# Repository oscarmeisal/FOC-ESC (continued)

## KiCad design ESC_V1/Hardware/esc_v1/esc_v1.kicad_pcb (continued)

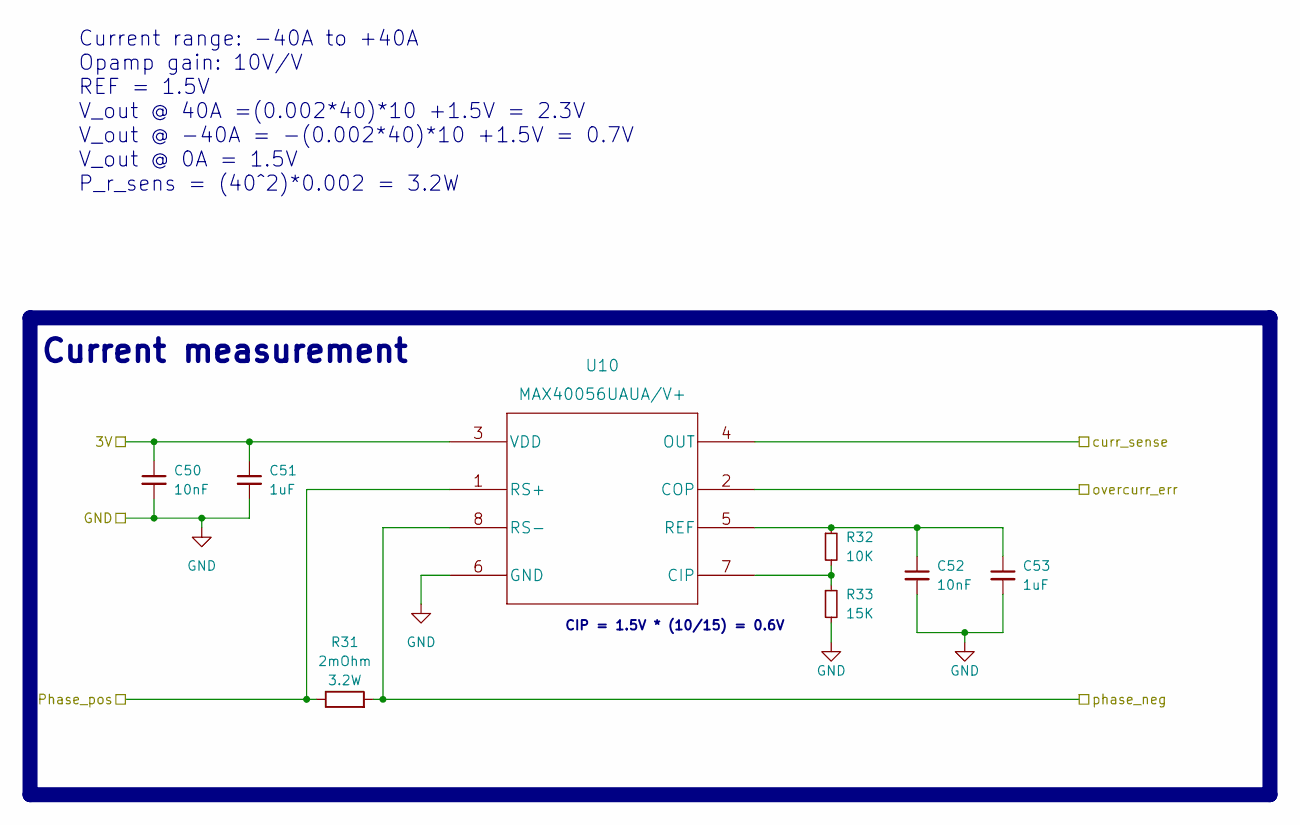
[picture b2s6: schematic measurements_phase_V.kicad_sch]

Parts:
C50, C52: 10nF; C_0603_1608Metric
C51, C53: 1uF; C_0603_1608Metric
R31: 2mOhm; WSHM28185L000FEA; Part no WSHM28182L000FEA
R32: 10K; R_0603_1608Metric
R33: 15K; R_0603_1608Metric
U10: MAX40056UAUA/V+; MAX40056UAUA&slash_V&plus_

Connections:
/MCU/curr_sense_V: U10.4 (OUT); also elsewhere on the board
/MCU/overcurr_err_V: U10.2 (COP); also elsewhere on the board
/PHASE_V: R31.2, U10.8 (RS-); also elsewhere on the board
/Powerstage/Gate_driver_phase_V/HS: R31.1, U10.1 (RS+); also elsewhere on the board
GND: C50.2, C51.2, C52.2, C53.2, R33.2, U10.6 (GND); also elsewhere on the board
unnamed: C52.1, C53.1, R32.1, U10.5 (REF)
unnamed: R32.2, R33.1, U10.7 (CIP)

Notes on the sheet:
Current range: -40A to +40A Opamp gain: 10V/V REF = 1.5V V_out @ 40A =(0.002*40)*10 +1.5V = 2.3V V_out @ -40A = -(0.002*40)*10 +1.5V = 0.7V V_out @ 0A = 1.5V P_r_sens = (40^2)*0.002 = 3.2W
Current measurement
CIP = 1.5V * (10/15) = 0.6V

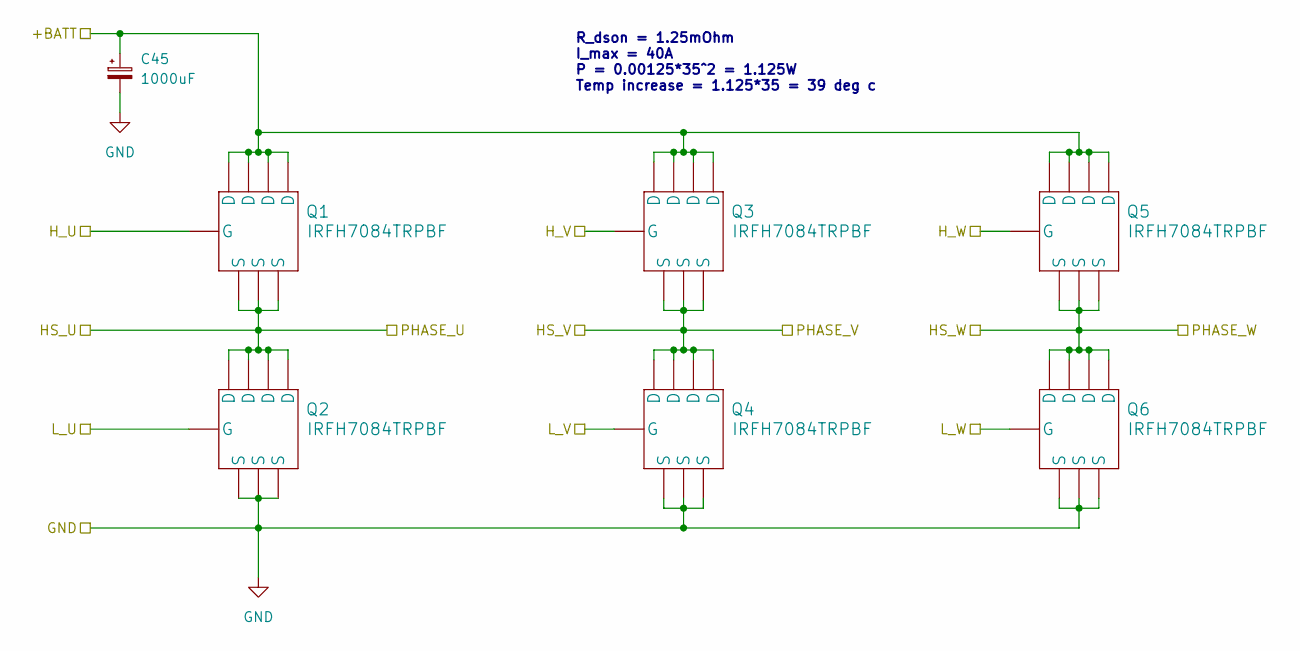
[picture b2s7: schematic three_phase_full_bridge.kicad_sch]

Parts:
C45: 1000uF; CP_Radial_D10.0mm_P5.00mm
Q1, Q2, Q3, Q4, Q5, Q6: IRFH7084TRPBF

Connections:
+BATT: C45.1, Q1.5 (D), Q1.6 (D), Q1.7 (D), Q1.8 (D), Q3.5 (D), Q3.6 (D), Q3.7 (D), Q3.8 (D), Q5.5 (D), Q5.6 (D), Q5.7 (D), Q5.8 (D); also elsewhere on the board
/PHASE_W: Q5.1 (S), Q5.2 (S), Q5.3 (S), Q6.5 (D), Q6.6 (D), Q6.7 (D), Q6.8 (D); also elsewhere on the board
/Powerstage/Gate_driver_phase_U/HO: Q1.4 (G); also elsewhere on the board
/Powerstage/Gate_driver_phase_U/HS: Q1.1 (S), Q1.2 (S), Q1.3 (S), Q2.5 (D), Q2.6 (D), Q2.7 (D), Q2.8 (D); also elsewhere on the board
/Powerstage/Gate_driver_phase_U/LO: Q2.4 (G); also elsewhere on the board
/Powerstage/Gate_driver_phase_V/HO: Q3.4 (G); also elsewhere on the board
/Powerstage/Gate_driver_phase_V/HS: Q3.1 (S), Q3.2 (S), Q3.3 (S), Q4.5 (D), Q4.6 (D), Q4.7 (D), Q4.8 (D); also elsewhere on the board
/Powerstage/Gate_driver_phase_V/LO: Q4.4 (G); also elsewhere on the board
/Powerstage/Gate_driver_phase_W/HO: Q5.4 (G); also elsewhere on the board
/Powerstage/Gate_driver_phase_W/LO: Q6.4 (G); also elsewhere on the board
GND: C45.2, Q2.1 (S), Q2.2 (S), Q2.3 (S), Q4.1 (S), Q4.2 (S), Q4.3 (S), Q6.1 (S), Q6.2 (S), Q6.3 (S); also elsewhere on the board

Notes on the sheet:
R_dson = 1.25mOhm I_max = 40A P = 0.00125*35^2 = 1.125W Temp increase = 1.125*35 = 39 deg c

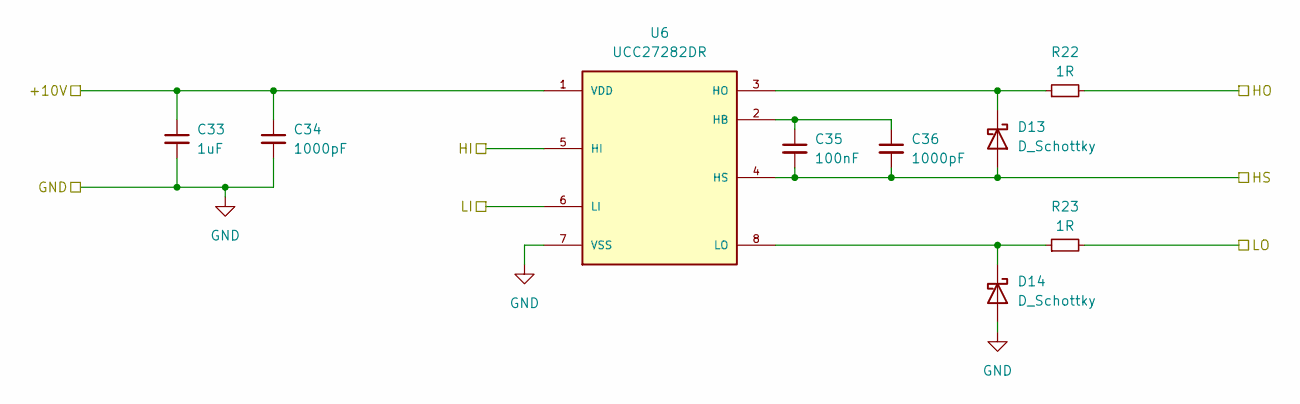
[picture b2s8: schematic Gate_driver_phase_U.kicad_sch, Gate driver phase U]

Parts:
C33: 1uF; C_0603_1608Metric
C34, C36: 1000pF; C_0603_1608Metric
C35: 100nF; C_0603_1608Metric
D13, D14: D_Schottky; SS2P4M384A; Part no SS2P4-M3/84A
R22, R23: 1R; R_0603_1608Metric
U6: UCC27282DR; SOIC127P599X175-8N; PARTREV A

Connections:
/MCU/PWM_H0: U6.5 (HI); also elsewhere on the board
/MCU/PWM_L0: U6.6 (LI); also elsewhere on the board
/Powerstage/Gate_driver_phase_U/GD_HB: C35.1, C36.1, U6.2 (HB)
/Powerstage/Gate_driver_phase_U/GD_HS: D13.1 (K), R22.1, U6.3 (HO)
/Powerstage/Gate_driver_phase_U/GD_LO: D14.1 (K), R23.1, U6.8 (LO)
/Powerstage/Gate_driver_phase_U/HO: R22.2; also elsewhere on the board
/Powerstage/Gate_driver_phase_U/HS: C35.2, C36.2, D13.2 (A), U6.4 (HS); also elsewhere on the board
/Powerstage/Gate_driver_phase_U/LO: R23.2; also elsewhere on the board
GND: C33.2, C34.2, D14.2 (A), U6.7 (VSS); also elsewhere on the board

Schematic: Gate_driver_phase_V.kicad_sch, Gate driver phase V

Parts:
C37: 1uF; C_0603_1608Metric
C38, C40: 1000pF; C_0603_1608Metric
C39: 100nF; C_0603_1608Metric
D15, D16: D_Schottky; SS2P4M384A; Part no SS2P4-M3/84A
R24, R25: 1R; R_0603_1608Metric
U7: UCC27282DR; SOIC127P599X175-8N; PARTREV A

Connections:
/MCU/PWM_H1: U7.5 (HI); also elsewhere on the board
/MCU/PWM_L1: U7.6 (LI); also elsewhere on the board
/Powerstage/Gate_driver_phase_V/GD_HB: C39.1, C40.1, U7.2 (HB)
/Powerstage/Gate_driver_phase_V/GD_HS: D15.1 (K), R24.1, U7.3 (HO)
/Powerstage/Gate_driver_phase_V/GD_LO: D16.1 (K), R25.1, U7.8 (LO)
/Powerstage/Gate_driver_phase_V/HO: R24.2; also elsewhere on the board
/Powerstage/Gate_driver_phase_V/HS: C39.2, C40.2, D15.2 (A), U7.4 (HS); also elsewhere on the board
/Powerstage/Gate_driver_phase_V/LO: R25.2; also elsewhere on the board
GND: C37.2, C38.2, D16.2 (A), U7.7 (VSS); also elsewhere on the board

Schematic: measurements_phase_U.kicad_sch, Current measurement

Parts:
C46, C48: 10nF; C_0603_1608Metric
C47, C49: 1uF; C_0603_1608Metric
R28: 2mOhm; WSHM28185L000FEA; Part no WSHM28182L000FEA
R29: 10K; R_0603_1608Metric
R30: 15K; R_0603_1608Metric
U9: MAX40056UAUA/V+; MAX40056UAUA&slash_V&plus_

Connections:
/MCU/curr_sense_U: U9.4 (OUT); also elsewhere on the board
/MCU/overcurr_err_U: U9.2 (COP); also elsewhere on the board
/PHASE_U: R28.2, U9.8 (RS-); also elsewhere on the board
/Powerstage/Gate_driver_phase_U/HS: R28.1, U9.1 (RS+); also elsewhere on the board
GND: C46.2, C47.2, C48.2, C49.2, R30.2, U9.6 (GND); also elsewhere on the board
unnamed: C48.1, C49.1, R29.1, U9.5 (REF)
unnamed: R29.2, R30.1, U9.7 (CIP)

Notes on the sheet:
Current measurement
CIP = 1.5V * (10/15) = 0.6V
Current range: -40A to +40A Opamp gain: 10V/V REF = 1.5V V_out @ 40A =(0.002*40)*10 +1.5V = 2.3V V_out @ -40A = -(0.002*40)*10 +1.5V = 0.7V V_out @ 0A = 1.5V P_r_sens = (40^2)*0.002 = 3.2W

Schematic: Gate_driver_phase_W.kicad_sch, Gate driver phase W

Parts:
C41: 1uF; C_0603_1608Metric
C42, C44: 1000pF; C_0603_1608Metric
C43: 100nF; C_0603_1608Metric
D17, D18: D_Schottky; SS2P4M384A; Part no SS2P4-M3/84A
R26, R27: 1R; R_0603_1608Metric
U8: UCC27282DR; SOIC127P599X175-8N; PARTREV A

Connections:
/MCU/PWM_H2: U8.5 (HI); also elsewhere on the board
/MCU/PWM_L2: U8.6 (LI); also elsewhere on the board
/PHASE_W: C43.2, C44.2, D17.2 (A), U8.4 (HS); also elsewhere on the board
/Powerstage/Gate_driver_phase_W/GD_HB: C43.1, C44.1, U8.2 (HB)
/Powerstage/Gate_driver_phase_W/GD_HS: D17.1 (K), R26.1, U8.3 (HO)
/Powerstage/Gate_driver_phase_W/GD_LO: D18.1 (K), R27.1, U8.8 (LO)
/Powerstage/Gate_driver_phase_W/HO: R26.2; also elsewhere on the board
/Powerstage/Gate_driver_phase_W/LO: R27.2; also elsewhere on the board
GND: C41.2, C42.2, D18.2 (A), U8.7 (VSS); also elsewhere on the board

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
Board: 4 copper layers, 127 parts (47 on the bottom side), 72 nets, no tracks yet.

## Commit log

2022-08-04 Components roughly placed in layout
2022-08-05 Fixing footprints
2022-08-16 changed gate driver, removed 10V buck and 5V LDO, added 5V buck. Started on Layout
2022-08-26 Continued on layout
2022-08-28 Changed to 6 layer pcb, increased space by 10mm, redid gate driver traces and power planes
2022-08-29 Finished layout. Final check remains
2022-08-30 Removed USB to serial chip and added serial connector. Finished layout, made production files and sent to production
